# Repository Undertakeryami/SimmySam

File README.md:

# SimmySam
This is a hackpad which is cool and coooool!!! (lol)
This consist of 5 keys and a small cute display and a microcontroller (ofc) hehe
and this would be programmed to like play certain combinations and then would also would like do cool stuff, like playing different voices, animations, didfferent functions in computer and a small mini game!!!
it would sure be worth it!! hehe thanks, 
below are the pictures of the pcb.

3d view of the PCB

The PCB blue print

Schematic represeintation of the PCB

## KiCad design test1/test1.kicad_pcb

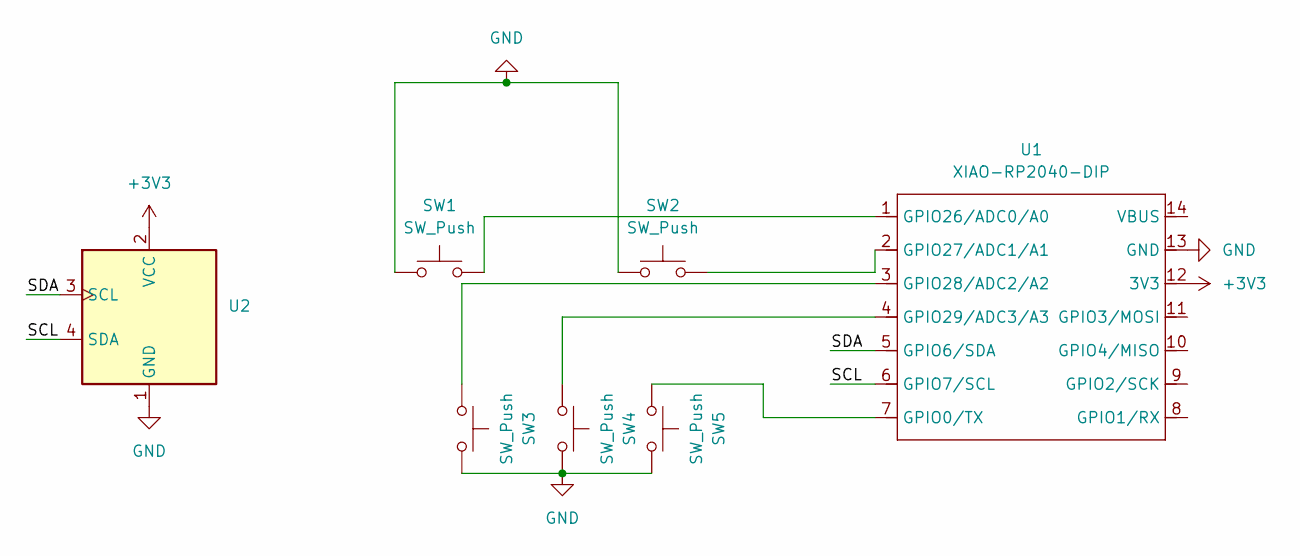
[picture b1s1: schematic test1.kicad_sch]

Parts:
SW1, SW2, SW3, SW4, SW5: SW_Push; SW_Cherry_MX_1.00u_PCB
U1: XIAO-RP2040-DIP
U2: ER_OLEDM0.91_1x-I2C

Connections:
+3V3: U1.12 (3V3), U2.2 (VCC)
/SCL: U1.6 (GPIO7/SCL), U2.4 (SDA)
/SDA: U1.5 (GPIO6/SDA), U2.3 (SCL)
GND: SW1.1, SW2.1, SW3.2, SW4.2, SW5.2, U1.13 (GND), U2.1 (GND)
unnamed: SW5.1, U1.7 (GPIO0/TX)
unnamed: SW1.2, U1.1 (GPIO26/ADC0/A0)
unnamed: SW2.2, U1.2 (GPIO27/ADC1/A1)
unnamed: SW3.1, U1.3 (GPIO28/ADC2/A2)
unnamed: SW4.1, U1.4 (GPIO29/ADC3/A3)

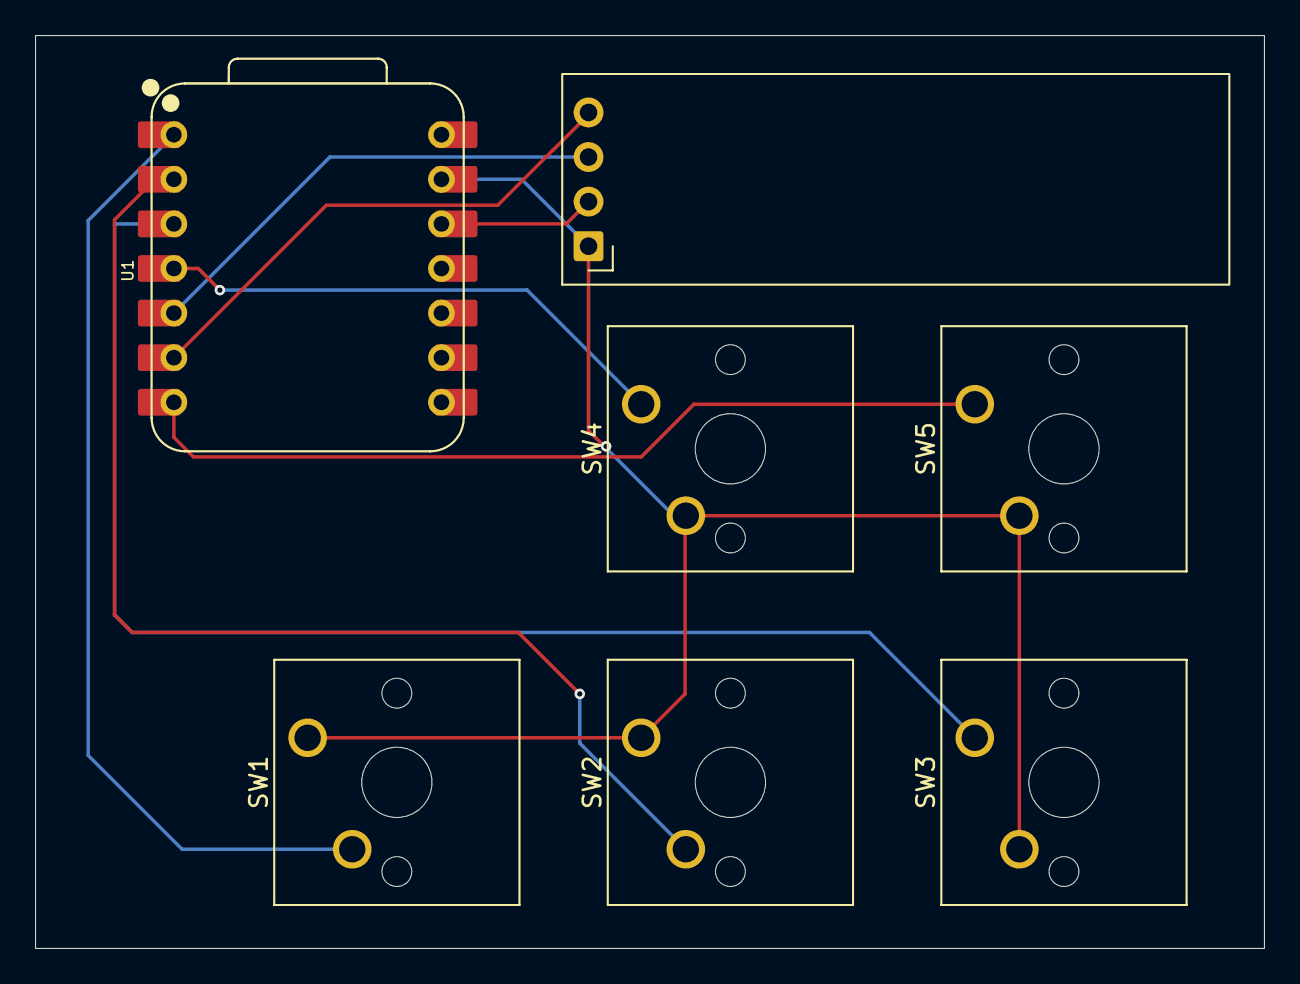
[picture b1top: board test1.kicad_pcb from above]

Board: 2 copper layers, 70.0 x 52.0 mm, 7 parts (0 on the bottom side), 9 nets.

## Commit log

2026-04-18 Uploaded the project
